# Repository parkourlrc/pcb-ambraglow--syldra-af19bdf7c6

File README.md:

# Syldra  
A room thermostat with home-assistant support, with a cute E-Ink screen for displaying data, a knob for setting target temperature and sensors for periodic measurements.
  
Firmware currently W.I.P.

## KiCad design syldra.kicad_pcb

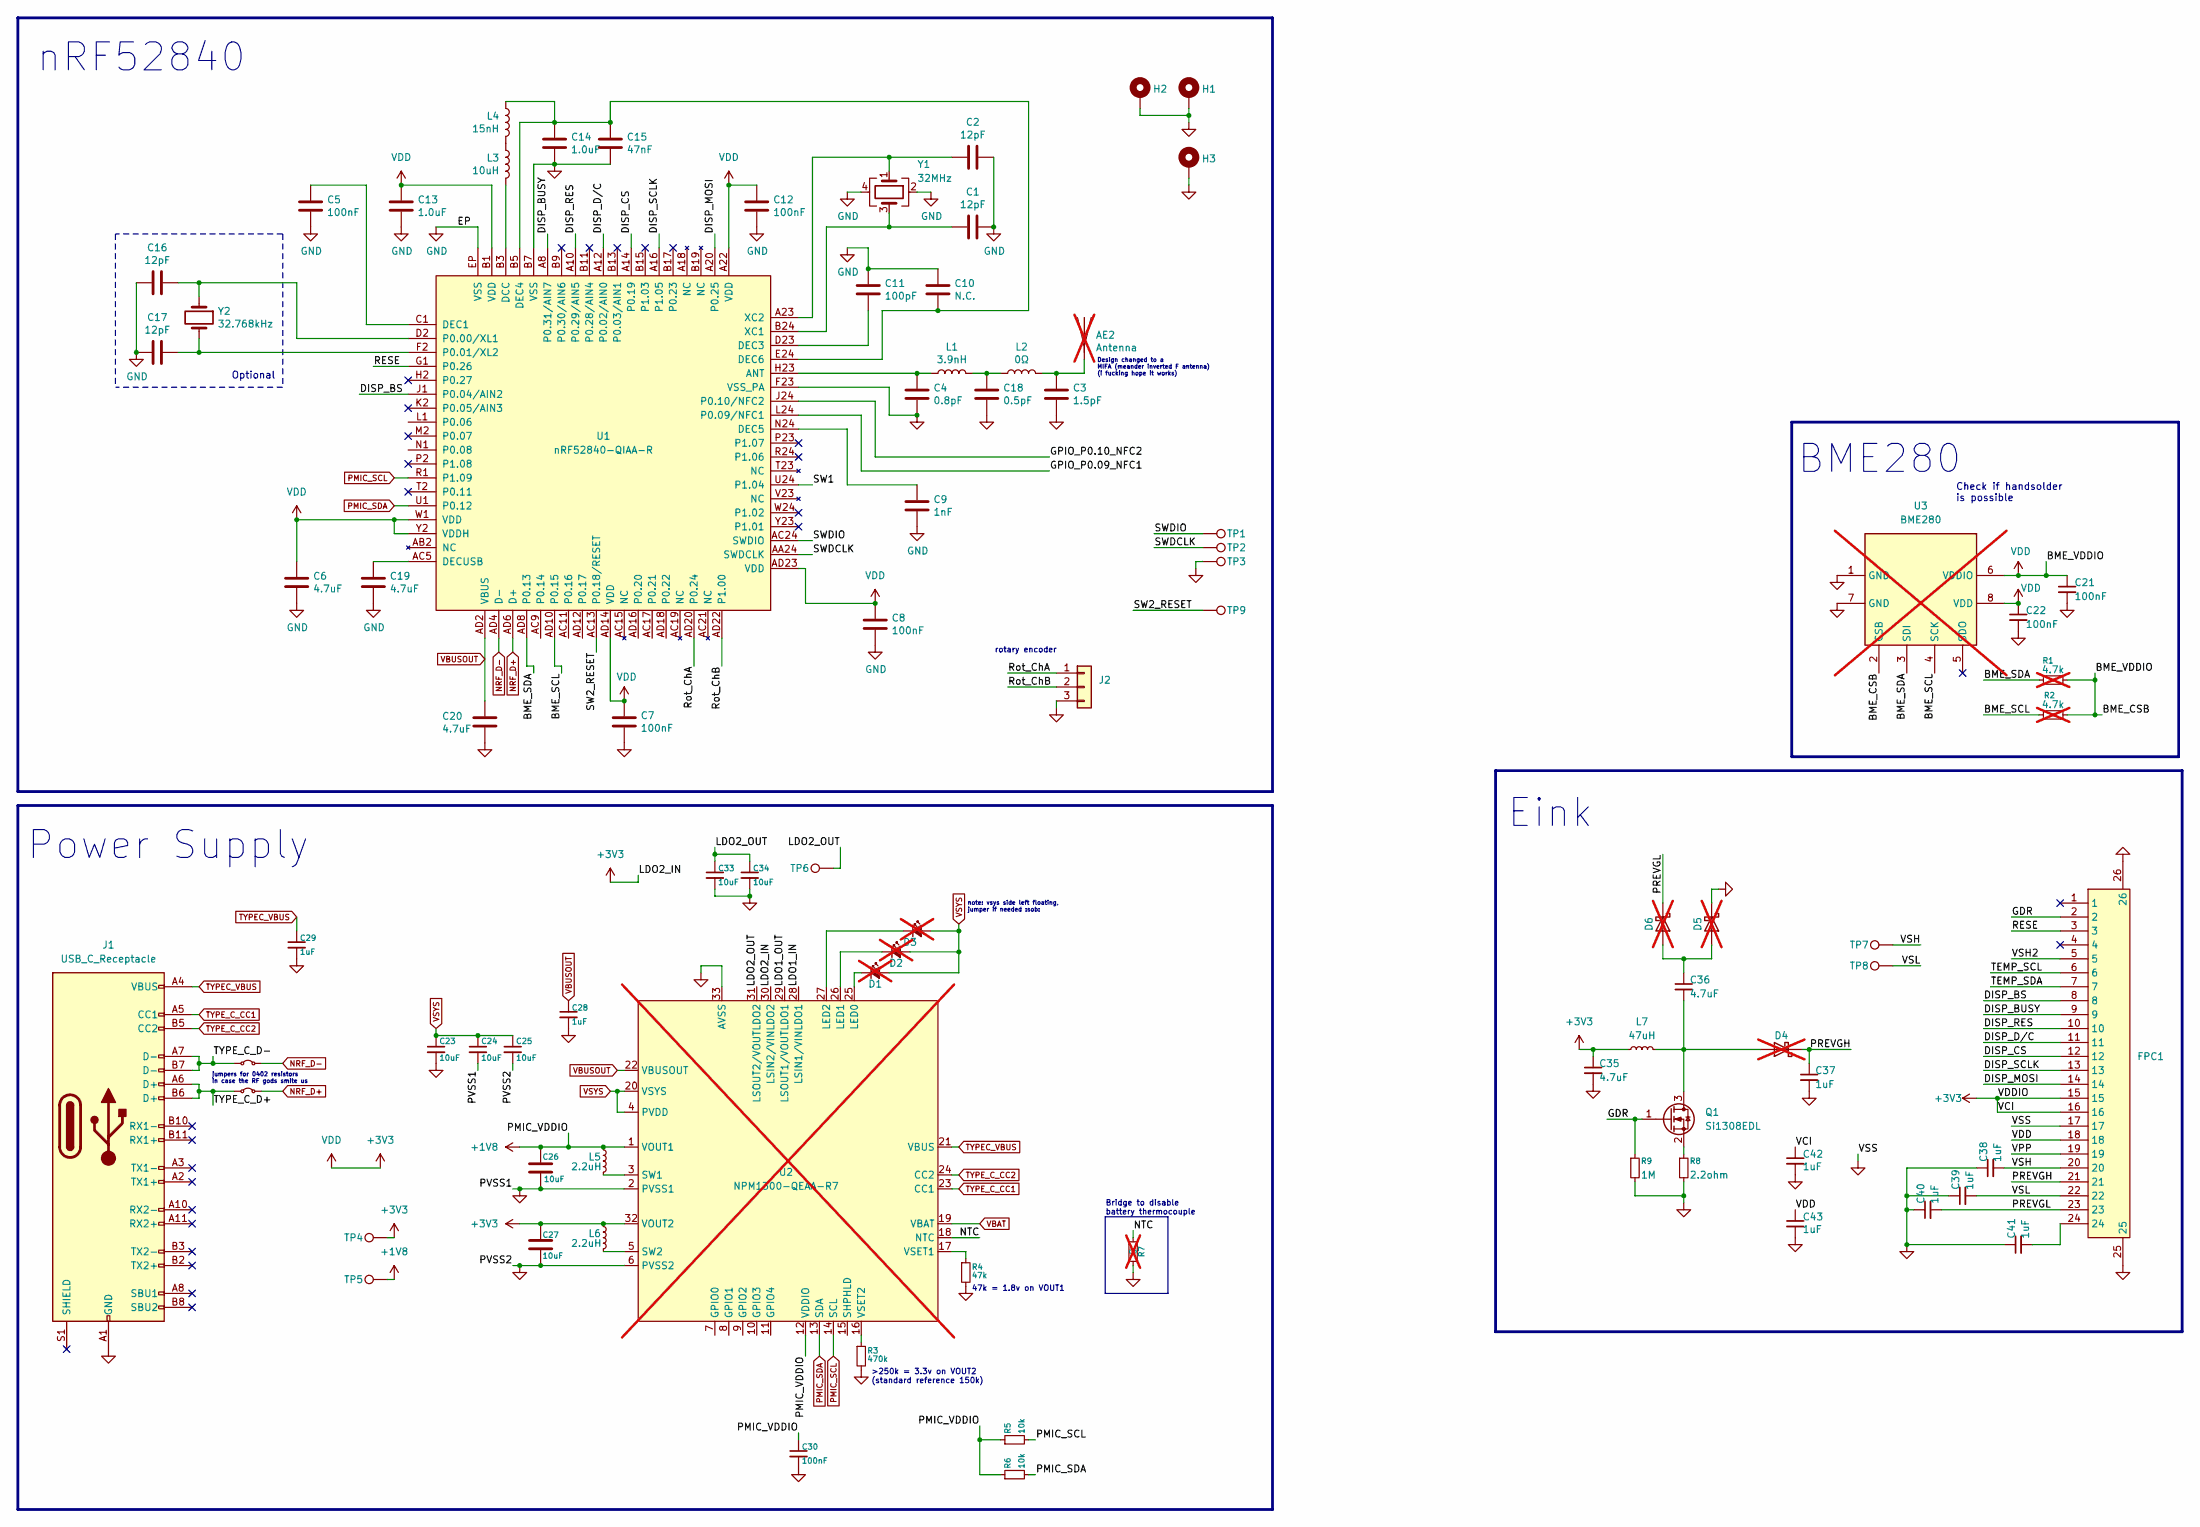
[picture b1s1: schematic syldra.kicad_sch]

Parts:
AE2: Antenna; 2.4GHz-meander_antenna; not fitted
C1, C2, C16, C17: 12pF; C_0402_1005Metric; MPN GCM1555C1H120GA16D
C3: 1.5pF; C_0402_1005Metric; MPN GCQ1555C1HR80WB01D
C4: 0.8pF; C_0402_1005Metric; MPN GCQ1555C1HR50WB01D
C5, C7, C8, C12: 100nF; C_0402_1005Metric; MPN GCM155R71C104KA55J
C6, C19, C20: 4.7uF; C_0603_1608Metric; MPN GCJ188C70J475KE02D
C9: 1nF; C_0402_1005Metric; MPN GCM1555C1H821JA16D
C10: N.C.; C_0402_1005Metric
C11: 100pF; C_0402_1005Metric; MPN GCM1555C1H101JA16D
C13, C14: 1.0uF; C_0603_1608Metric; MPN GCM188R71C105KA64D
C15: 47nF; C_0603_1608Metric; MPN GCM155R71E473KA55D
C18: 0.5pF; C_0402_1005Metric; MPN GCQ1555C1HR80WB01D
C21, C22, C30: 100nF; C_0402_1005Metric
C23, C24, C25, C26, C27, C33, C34: 10uF; C_0603_1608Metric
C28, C29: 1uF; C_0603_1608Metric
C35, C36: 4.7uF; C_0402_1005Metric
C37, C38, C39, C40, C41, C42, C43: 1uF; C_0402_1005Metric
D1, D2, D3: LED_Small_Filled; LED_0603_1608Metric; not fitted
D4, D5, D6: MBR0530; D_SOD-123; not fitted
FPC1: AFC24-S24FIC-00; FPC-SMD_P0.50-24P_QCHF-SM-H2.0; LCSC Part C262292
H1, H2, H3: MountingHole_Pad; MountingHole_2.1mm
J1: USB_C_Receptacle; USB-C-SMD_HANELECTRICITY_161N-4XVS11
J2: Conn_01x03; PinHeader_1x03_P2.54mm_Vertical
JP1, JP2: Jumper_2_Small_Bridged; R0402_bridged
L1: 3.9nH; L_0402_1005Metric; MPN LQW15AN4N7C0ZD
L2: 0Ω; L_0402_1005Metric; MPN AC0402FR-070RL
L3: 10uH; L_0603_1608Metric; MPN KLZ1608MHR100WTD25
L4: 15nH; L_0402_1005Metric; MPN MLK1005S15NJTD25
L5, L6: 2.2uH; L0806
L7: 47uH; L_Taiyo-Yuden_MD-4040
Q1: Si1308EDL; SOT-323_SC-70
R1, R2: 4.7k; R_0402_1005Metric; not fitted
R3: 470k; R_0402_1005Metric
R4: 47k; R_0402_1005Metric
R5, R6: 10k; R_0402_1005Metric
R7: 0; not fitted
R8: 2.2ohm; R_0603_1608Metric
R9: 1M; R_0402_1005Metric
TP1, TP2, TP4, TP5, TP6, TP7, TP8, TP9: TestPoint; TestPoint_Pad_D1.0mm
TP3: TestPoint; TestPoint_Pad_D1.5mm
U1: nRF52840-QIAA-R; Nordic_AQFN-73-1EP_7x7mm_P0.5mm; MPN NRF52840-QIAA-R
U2: NPM1300-QEAA-R7; QFN-32_L5.0-W5.0-P0.50-TL-EP3.5; LCSC Part C7501206; not fitted
U3: BME280; Bosch_LGA-8_2.5x2.5mm_P0.65mm_ClockwisePinNumbering; not fitted
Y1: 32MHz; Crystal_SMD_2016-4Pin_2.0x1.6mm; MPN CX2016DB32000D0WZRC1
Y2: 32.768kHz; Crystal_SMD_3215-2Pin_3.2x1.5mm; MPN ECS-.327-9-12QS-TR

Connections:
+1V8: C26.1, C30.1, L5.1, R5.1, R6.1, TP5.1, U2.1 (VOUT1), U2.12 (VDDIO)
+3V3: C6.1, C7.1, C8.1, C12.1, C13.1, C21.1, C22.1, C27.1, C35.1, C42.1, C43.1, FPC1.15, FPC1.16, FPC1.18, L6.1, L7.1, R1.2, R2.2, TP4.1, U1.A22 (VDD), U1.AD14 (VDD), U1.AD23 (VDD), U1.B1 (VDD), U1.W1 (VDD), U1.Y2 (VDDH), U2.30 (LSIN2/VINLDO2), U2.32 (VOUT2), U3.2 (CSB), U3.6 (VDDIO), U3.8 (VDD)
/BME_SCL: R2.1, U1.AD10 (P0.15), U3.4 (SCK)
/BME_SDA: R1.1, U1.AD8 (P0.13), U3.3 (SDI)
/DISP_BS: FPC1.8, U1.J1 (P0.04/AIN2)
/DISP_BUSY: FPC1.9, U1.A8 (P0.31/AIN7)
/DISP_CS: FPC1.12, U1.A14 (P0.19)
/DISP_D/C: FPC1.11, U1.A12 (P0.02/AIN0)
/DISP_MOSI: FPC1.14, U1.A20 (P0.25)
/DISP_RES: FPC1.10, U1.A10 (P0.29/AIN5)
/DISP_SCLK: FPC1.13, U1.A16 (P1.05)
/GDR: FPC1.2, Q1.1 (G), R9.1
/GPIO_P0.09_NFC1: U1.L24 (P0.09/NFC1)
/GPIO_P0.10_NFC2: U1.J24 (P0.10/NFC2)
/LDO1_IN: U2.28 (LSIN1/VINLDO1)
/LDO1_OUT: U2.29 (LSOUT1/VOUTLDO1)
/LDO2_OUT: C33.1, C34.1, TP6.1, U2.31 (LSOUT2/VOUTLDO2)
/NTC: R7.1, U2.18 (NTC)
/PREVGH: C37.1, D4.1 (K), FPC1.21
/PREVGL: C40.2, D6.1 (K), FPC1.23
/RESE: FPC1.3, U1.G1 (P0.26)
/Rot_ChA: J2.1, U1.AD20 (P0.24)
/Rot_ChB: J2.2, U1.AD22 (P1.00)
/SW1: U1.U24 (P1.04)
/SW2_RESET: TP9.1, U1.AC13 (P0.18/RESET)
/SWDCLK: TP2.1, U1.AA24 (SWDCLK)
/SWDIO: TP1.1, U1.AC24 (SWDIO)
/TEMP_SCL: FPC1.6
/TEMP_SDA: FPC1.7
/TYPE_C_D+: J1.A6 (D+), J1.B6 (D+), JP2.1 (A)
/TYPE_C_D-: J1.A7 (D-), J1.B7 (D-), JP1.1 (A)
/VPP: FPC1.19
/VSH: C38.2, FPC1.20, TP7.1
/VSH2: FPC1.5
/VSL: C39.2, FPC1.22, TP8.1
GND: C1.1, C2.1, C3.2, C4.2, C5.2, C6.2, C7.2, C8.2, C9.2, C10.2, C11.2, C12.2, C13.2, C14.2, C15.2, C16.2, C17.2, C18.2, C19.2, C20.2, C21.2, C22.2, C23.2, C24.2, C25.2, C26.2, C27.2, C28.2, C29.2, C30.2, C33.2, C34.2, C35.2, C37.2, C38.1, C39.1, C40.1, C41.1, C42.2, C43.2, D5.1 (K), FPC1.17, FPC1.25, FPC1.26, H1.1, H2.1, H3.1, J1.A1 (GND), J1.A12 (GND), J1.B1 (GND), J1.B12 (GND), J2.3, R3.2, R4.2, R7.2, R8.2, R9.2, TP3.1, U1.B7 (VSS), U1.EP (VSS), U1.F23 (VSS_PA), U2.2 (PVSS1), U2.6 (PVSS2), U2.33 (AVSS), U3.1 (GND), U3.7 (GND), Y1.2, Y1.4; also elsewhere on the board
NRF_D+: JP2.2 (B), U1.AD6 (D+)
NRF_D-: JP1.2 (B), U1.AD4 (D-)
unnamed: AE2.1 (A), C3.1, L2.2
unnamed: C18.1, L1.1, L2.1
unnamed: C41.2, FPC1.24
unnamed: D1.1 (K), U2.25 (LED0)
unnamed: D2.1 (K), U2.26 (LED1)
unnamed: D3.1 (K), U2.27 (LED2)
unnamed: C36.2, D4.2 (A), L7.2, Q1.3 (D)
unnamed: C36.1, D5.2 (A), D6.2 (A)
unnamed: L3.2, L4.1
unnamed: Q1.2 (S), R8.1
unnamed: C4.1, L1.2, U1.H23 (ANT)
unnamed: L3.1, U1.B3 (DCC)
unnamed: C5.1, U1.C1 (DEC1)
unnamed: C11.1, U1.D23 (DEC3)
unnamed: C10.1, C14.1, C15.1, L4.2, U1.B5 (DEC4), U1.E24 (DEC6)
unnamed: C9.1, U1.N24 (DEC5)
unnamed: C19.1, U1.AC5 (DECUSB)
unnamed: C16.1, U1.D2 (P0.00/XL1), Y2.1
unnamed: C17.1, U1.F2 (P0.01/XL2), Y2.2
unnamed: C1.2, U1.B24 (XC1), Y1.3
unnamed: C2.2, U1.A23 (XC2), Y1.1
unnamed: L5.2, U2.3 (SW1)
unnamed: L6.2, U2.5 (SW2)
unnamed: R4.1, U2.17 (VSET1)
unnamed: R3.1, U2.16 (VSET2)
PMIC_SCL: R5.2, U1.R1 (P1.09), U2.14 (SCL)
PMIC_SDA: R6.2, U1.U1 (P0.12), U2.13 (SDA)
TYPEC_VBUS: C29.1, J1.A4 (VBUS), J1.A9 (VBUS), J1.B4 (VBUS), J1.B9 (VBUS), U2.21 (VBUS)
TYPE_C_CC1: J1.A5 (CC1), U2.23 (CC1)
TYPE_C_CC2: J1.B5 (CC2), U2.24 (CC2)
VBAT: U2.19 (VBAT); also elsewhere on the board
VBUSOUT: C20.1, C28.1, U1.AD2 (VBUS), U2.22 (VBUSOUT)
VSYS: C23.1, C24.1, C25.1, D1.2 (A), D2.2 (A), D3.2 (A), U2.4 (PVDD), U2.20 (VSYS)

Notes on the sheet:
47k = 1.8v on VOUT1
BME280
Bridge to disable battery thermocouple
nRF52840
note: vsys side left floating, jumper if needed :sob:
rotary encoder
Optional
Eink
Design changed to a MIFA (meander inverted F antenna) (i fucking hope it works)
Power Supply
jumpers for 0402 resistors in case the RF gods smite us
Check if handsolder is possible
>250k = 3.3v on VOUT2 (standard reference 150k)

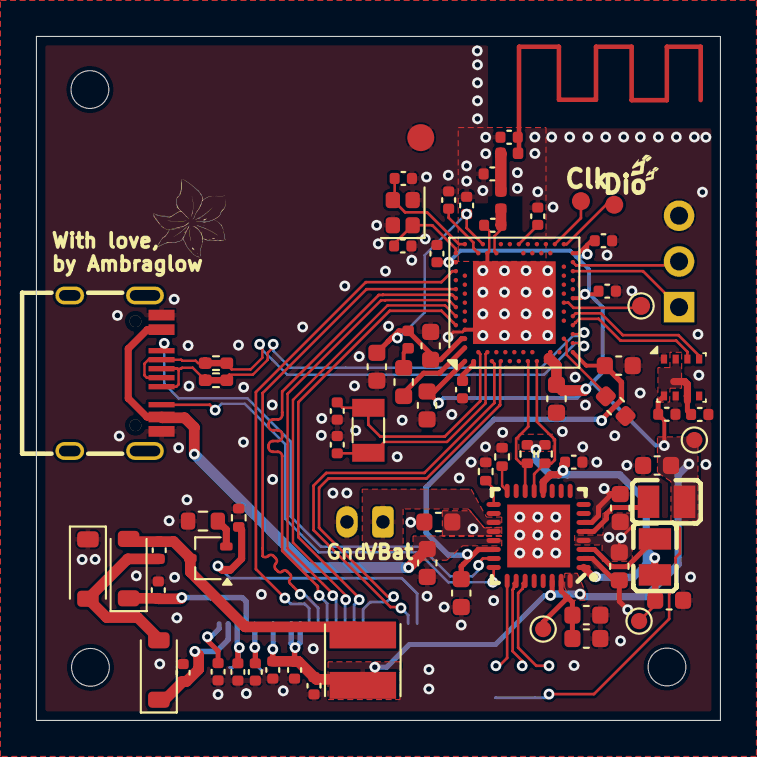
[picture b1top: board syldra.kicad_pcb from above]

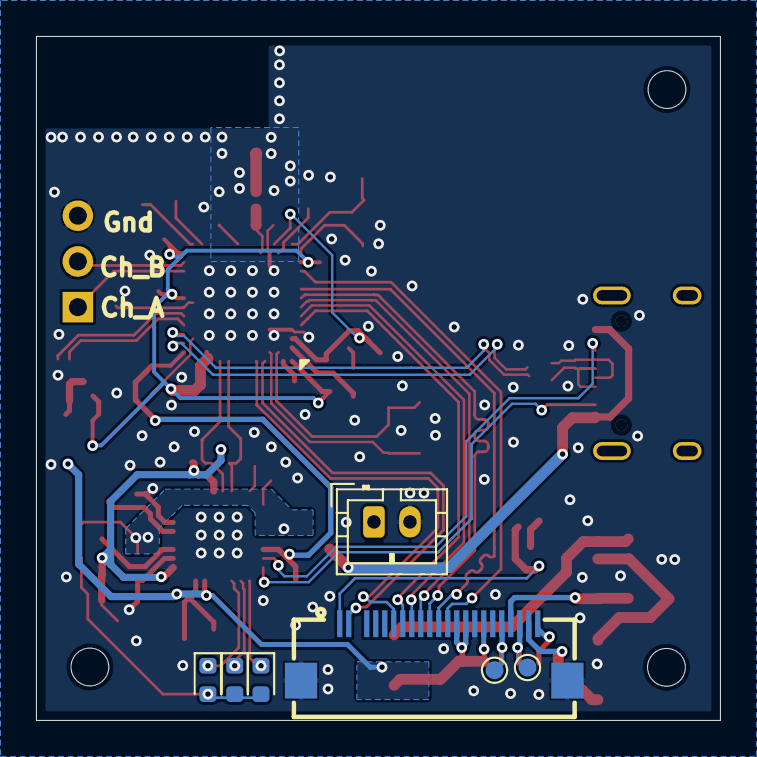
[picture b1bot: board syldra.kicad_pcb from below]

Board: 2 copper layers, 38.0 x 38.0 mm, 85 parts (7 on the bottom side), 61 nets.

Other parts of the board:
J3: Conn_01x02; JST_PH_B2B-PH-K_1x02_P2.00mm_Vertical

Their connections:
GND: J3.2; also elsewhere on the board
VBAT: J3.1; also elsewhere on the board

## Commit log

2026-01-27 refactor: project rename
2026-01-27 chore(workflows): .kicad_pcb name change
2026-01-27 chore: adding a LICENSE
2026-01-27 chore: README update
2026-01-27 chore: update README
